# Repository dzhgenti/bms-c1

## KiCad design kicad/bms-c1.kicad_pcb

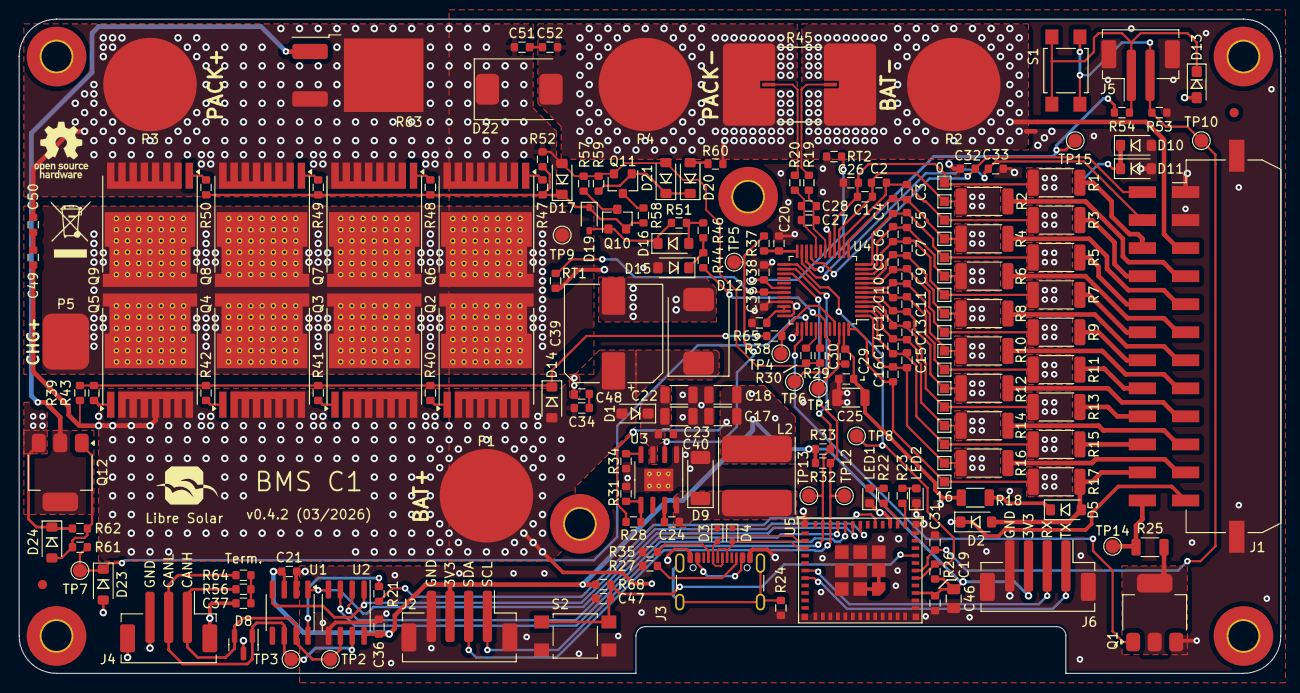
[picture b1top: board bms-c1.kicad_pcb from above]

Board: 4 copper layers, 135.0 x 70.0 mm, 209 parts (0 on the bottom side), 118 nets.

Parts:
C1, C2, C3, C4, C5, C6, C7, C8, C9, C10, C11, C12, C13, C14, C15, C16, C26: 220nF; C_0603_1608
C17, C18: 47µF; C_1206_3216
C19, C21, C24, C28, C31, C34, C36, C37, C40, C48, C49, C50, C51, C52: 100nF; C_0603_1608
C20: 2.2µF; C_0603_1608
C22, C23: 2.2µF; C_1206_3216
C25: 1µF; C_1206_3216
C27, C29, C32, C33, C35, C38: 100pF; C_0603_1608
C30, C47: 1µF; C_0603_1608
C39: 47uF; CP_Elec_10x10
C46: 10µF; C_0805_2012
D1, D13: PMEG10010ELRX; D_SOD-123F
D2, D5, D10, D15, D16, D20: BAT46W; D_SOD-123
D3, D4: ESD5B5.0ST1G; D_SOD-523
D8: PESD2CANFD; SOT-23
D9: VSS8D3M10-M3/I; D_SOD-128
D11: 3.6V; D_SOD-123
D12: SMCJ70A; D_SMC
D14, D17, D21, D24: 16V; D_SOD-123
D19: 5.1V; D_SOD-323
D22: MURS360; D_SMC
D23: 75V; D_SOD-123
FID1, FID2: Fiducial; Fiducial_1mm_Mask2mm
H1, H2, H3, H4, H5, H6: MountingHole; MountingHole_3.2mm_M3_Pad_TopBottom
J1: MicroFit 2x12; Molex_Micro-Fit_3.0_43045-2410_2x12-1MP_P3.00mm_Horizontal
J2, J6: B4B-PH-SM4; JST_PH_B4B-PH-SM4-TB_1x04-1MP_P2.00mm_Vertical
J3: USB_C_Receptacle_USB2.0; USB_C_Receptacle_GCT_USB4105-xx-A_16P_TopMnt_Horizontal
J4: B3B-PH-SM4; JST_PH_B3B-PH-SM4-TB_1x03-1MP_P2.00mm_Vertical
J5: B2B-PH-SM4; JST_PH_B2B-PH-SM4-TB_1x02-1MP_P2.00mm_Vertical
L2: 22µH; Bourns_SRN8040TA
LED1: LED red; LED_0603_1608Metric
LED2: LED green; LED_0603_1608Metric
LOGO1: OPEN_HARDWARE; OSHW-Logo_5.7x6mm_SilkScreen
LOGO2: LIBRE_SOLAR; LIBRESOLAR_LOGO
NT1: NetTie; NetTie-2_SMD_Pad0.5mm
P1, P2, P3, P4: CONN_01X01; Wuerth_PowerOne_SMD_LF990005
P5: CONN_01X01; SolderWirePad_1x01_SMD_5x10mm
Q1: DMN10H220LE; SOT-223
Q2, Q3, Q4, Q5, Q6, Q7, Q8, Q9: IPT012N08N5; Infineon_PG-HSOF-8-1_ThermalVias
Q10: BSS84; SOT-23
Q11: BSS123N; SOT-23
Q12: ZXMP10A17GTA; SOT-223-3_TabPin2
R1, R2, R3, R4, R5, R6, R7, R8, R9, R10, R11, R12, R13, R14, R15, R16, R17: 20; R_2010_5025
R18: 100; R_1206_3216
R19, R20, R38, R44: 100; R_0603_1608
R21, R37: 0R; R_0603_1608
R22, R23, R46: 1k; R_0603_1608
R24, R26, R62: 1M; R_0603_1608
R25: 10; R_1206_3216
R27, R35, R53, R54: 5.1k; R_0603_1608
R28, R65: 82k; R_0603_1608
R29, R30, R60, R68: 10k; R_0603_1608
R31: 35.7k; R_0603_1608
R32, R33: 2.2k; R_0603_1608
R34: 52.3k; R_0603_1608
R39, R52, R59: 10M; R_0603_1608
R40, R41, R42, R43, R47, R48, R49, R50, R57: 47; R_0603_1608
R45: 300µ; R_Shunt_5931_Kelvin
R51, R61: 68k; R_0603_1608
R56, R64: 62R; R_0603_1608
R58: 470; R_0603_1608
R63: 40; Bourns_PWR163
RT1, RT2: 10k; R_0603_1608
S1, S2: SW_PUSH; SW_SPST_TL3305A
TP1, TP2, TP3, TP4, TP5, TP6, TP7, TP8, TP9, TP10, TP12, TP13, TP14, TP15: TestPoint; TestPoint_Pad_D1.5mm
TP16, TP17, TP18, TP19, TP20, TP21, TP22, TP23, TP24, TP25, TP26, TP27, TP28, TP29, TP30, TP31, TP32: TestPoint; TestPoint_Pad_1.0x1.0mm
U1: SN65HVD230; SOIC-8_3.9x4.9mm_P1.27mm
U2: SN65HVD75; SOIC-8_3.9x4.9mm_P1.27mm
U3: LMR38010; SOIC-8-1EP_3.9x4.9mm_P1.27mm_EP2.4x3.1mm_ThermalVias
U4: BQ76952; TQFP-48_7x7mm_P0.5mm
U5: ESP32-C3-MINI-1

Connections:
+3V3: C17.1, C18.1, C19.1, C21.1, C36.1, C46.1, D13.2 (A), J2.3, J6.3, L2.2, R26.2, R28.1, R32.2, R33.2, R68.2, U1.3 (VCC), U2.8 (VCC), U5.3 (3V3)
/BAT+: C34.1, C39.1, C49.1, D1.2 (A), D2.1 (K), D12.1 (K), D14.2 (A), J1.12, P1.1, Q2.2 (S), Q3.2 (S), Q4.2 (S), Q5.2 (S), R39.2
/BAT-: C39.2, C48.2, D12.2 (A), J1.3, NT1.1, P2.1, R45.1
/BQ76952/ALERT: R26.1, TP8.1, U4.25 (ALERT), U5.5 (GPIO2/ADC1_CH2)
/BQ76952/BAT: C25.1, C29.1, C30.2, R18.1, U4.47 (BAT)
/BQ76952/BTN_HIGH: D13.1 (K), J5.1, R54.1, S1.2
/BQ76952/CHG: R38.1, TP4.1, U4.45 (CHG)
/BQ76952/CP1: C30.1, TP1.1, U4.46 (CP1)
/BQ76952/DSG: R44.1, TP6.1, U4.43 (DSG)
/BQ76952/LD: R30.1, U4.41 (LD)
/BQ76952/PACK: R29.1, U4.42 (PACK)
/BQ76952/PDSG: D23.1 (K), R61.1, TP7.1, U4.39 (PDSG)
/BQ76952/SHUNT_N: R20.1, R45.3
/BQ76952/SHUNT_P: R19.1, R45.2
/BQ76952/SRN: C27.2, C28.2, R20.2, U4.20 (SRN)
/BQ76952/SRP: C27.1, C28.1, R19.2, U4.18 (SRP)
/BQ76952/TEMP_SHUNT: C38.1, RT2.2, U4.30 (DFETOFF)
/BQ76952/VC0: C1.2, C26.1, D10.1 (K), D11.1 (K), R1.2, TP16.1, U4.16 (VC0)
/BQ76952/VC1: C1.1, C2.2, R2.2, TP17.1, U4.15 (VC1)
/BQ76952/VC2: C2.1, C3.2, R3.2, TP18.1, U4.14 (VC2)
/BQ76952/VC3: C3.1, C4.2, R4.2, TP19.1, U4.13 (VC3)
/BQ76952/VC4: C4.1, C5.2, R5.2, TP20.1, U4.12 (VC4)
/BQ76952/VC5: C5.1, C6.2, R6.2, TP21.1, U4.11 (VC5)
/BQ76952/VC6: C6.1, C7.2, R7.2, TP22.1, U4.10 (VC6)
/BQ76952/VC7: C7.1, C8.2, R8.2, TP23.1, U4.9 (VC7)
/BQ76952/VC8: C8.1, C9.2, R9.2, TP24.1, U4.8 (VC8)
/BQ76952/VC9: C9.1, C10.2, R10.2, TP25.1, U4.7 (VC9)
/BQ76952/VC10: C10.1, C11.2, R11.2, TP26.1, U4.6 (VC10)
/BQ76952/VC11: C11.1, C12.2, R12.2, TP27.1, U4.5 (VC11)
/BQ76952/VC12: C12.1, C13.2, R13.2, TP28.1, U4.4 (VC12)
/BQ76952/VC13: C13.1, C14.2, R14.2, TP29.1, U4.3 (VC13)
/BQ76952/VC14: C14.1, C15.2, R15.2, TP30.1, U4.2 (VC14)
/BQ76952/VC15: C15.1, C16.2, R16.2, TP31.1, U4.1 (VC15)
/BQ76952/VC16: C16.1, R17.2, TP32.1, U4.48 (VC16)
/BQ76952/WAKE: R54.2, TP15.1, U4.22 (TS2)
/BTN_LOW: C31.2, J5.2, R53.2, S1.1, TP10.1, U5.6 (GPIO3/ADC1_CH3)
/C1+: J1.4, R2.1
/C1-: J1.15, R1.1
/C2+: J1.16, R3.1
/C3+: J1.5, R4.1
/C4+: J1.17, R5.1
/C5+: J1.6, R6.1
/C6+: J1.18, R7.1
/C7+: J1.7, R8.1
/C8+: J1.19, R9.1
/C9+: J1.8, R10.1
/C10+: J1.20, R11.1
/C11+: J1.9, R12.1
/C12+: J1.21, R13.1
/C13+: J1.10, R14.1
/C14+: J1.22, R15.1
/C15+: J1.11, R16.1
/C16+: D2.2 (A), D5.2 (A), J1.23, R17.1
/CAN_H: D8.2 (K), J4.1, R56.1, TP2.1, U1.7 (CANH), U2.6 (A)
/CAN_L: D8.1 (K), J4.2, R64.2, TP3.1, U1.6 (CANL), U2.7 (B)
/CHG+: D24.1 (K), P5.1, Q2.3 (D), Q3.3 (D), Q4.3 (D), Q5.3 (D), Q6.3 (D), Q7.3 (D), Q8.3 (D), Q9.3 (D), Q12.3 (S), R62.1, TP9.1
/ESP32-C3 MCU/CAN_RX: U1.4 (R), U2.1 (R), U5.18 (GPIO4/ADC1_CH4)
/ESP32-C3 MCU/CAN_STB: R21.2, U5.16 (GPIO10)
/ESP32-C3 MCU/CAN_TX: U1.1 (D), U2.4 (D), U5.19 (GPIO5/ADC2_CH0)
/ESP32-C3 MCU/NRST: C47.1, R68.1, S2.2, U5.8 (EN/CHIP_PU)
/ESP32-C3 MCU/RS485_DE: U2.3 (DE), U5.20 (GPIO6)
/ESP32-C3 MCU/RS485_~RE: U2.2 (~RE), U5.21 (GPIO7)
/ESP32-C3 MCU/USB_D+: D4.2 (A2), J3.A6 (D+), J3.B6 (D+), U5.27 (GPIO19/USB_D+)
/ESP32-C3 MCU/USB_D-: D3.2 (A2), J3.A7 (D-), J3.B7 (D-), U5.26 (GPIO18/USB_D-)
/FUSE: J1.24, R25.2, TP14.1
/I2C_SCL: J2.1, R33.1, TP13.1, U4.26 (SCL), U5.23 (GPIO9)
/I2C_SDA: J2.2, R32.1, TP12.1, U4.27 (SDA), U5.22 (GPIO8)
/LED_GREEN: R23.2, U5.12 (GPIO0/ADC1_CH0/XTAL_32K_P)
/LED_RED: R22.2, U5.13 (GPIO1/ADC1_CH1/XTAL_32K_N)
/PACK+: C50.2, C51.1, D17.2 (A), D21.2 (A), D22.1 (K), P3.1, Q6.2 (S), Q7.2 (S), Q8.2 (S), Q9.2 (S), Q11.2 (S), R29.2, R30.2, R52.2, R57.1, R59.2, R63.2, R63.3
/PACK-: C52.2, D22.2 (A), P4.1, R45.4, R60.1
/Power Part/CHG_G: D14.1 (K), R38.2, R39.1, R40.1, R41.1, R42.1, R43.1
/Power Part/DSG_G: D17.1 (K), D19.1 (K), Q10.2 (S), R47.2, R48.2, R49.2, R50.2, R52.1, R58.1
/Power Supply/EN: R37.1, TP5.1, U3.2 (EN)
/Power Supply/FB: R28.2, R31.1, U3.5 (FB)
/Power Supply/SW: C24.2, D9.1 (K), L2.1, U3.8 (SW)
/Power Supply/VIN: C22.1, C23.1, C40.1, D1.1 (K), U3.3 (VIN)
/REG18: C20.1, R37.2, U4.24 (REG18)
/TEMP1: C32.1, J1.13, U4.21 (TS1)
/TEMP2: C33.1, J1.14, U4.23 (TS3)
/TEMP_FETS: C35.1, RT1.2, U4.31 (DCHG)
/UART_RX: J6.2, U5.30 (GPIO20/U0RXD)
/UART_TX: J6.1, U5.31 (GPIO21/U0TXD)
GND: C17.2, C18.2, C19.2, C20.2, C21.2, C22.2, C23.2, C25.2, C26.2, C29.2, C31.1, C32.2, C33.2, C35.2, C36.2, C37.2, C38.2, C40.2, C46.2, C47.2, D3.1 (A1), D4.1 (A1), D8.3 (A), D9.2 (A), D10.2 (A), D11.2 (A), D15.2 (A), D23.2 (A), J1.1, J1.2, J1.MP (MountPin), J2.4, J2.MP (MountPin), J3.A1 (GND), J3.A12 (GND), J3.B1 (GND), J3.B12 (GND), J4.3, J4.MP (MountPin), J5.MP (MountPin), J6.4, J6.MP (MountPin), LED1.1 (K), LED2.1 (K), NT1.2, Q1.3 (S), R24.1, R27.1, R31.2, R34.2, R35.1, R53.1, R65.2, RT1.1, RT2.1, S2.1, U1.2 (GND), U2.5 (GND), U3.1 (GND), U3.9 (PADGND), U4.17 (VSS), U4.33 (RST_SHUT), U4.36 (REGIN), U4.37 (BREG), U5.1 (GND), U5.2 (GND), U5.11 (GND), U5.14 (GND), U5.36 (GND)
unnamed: C34.2, C48.1
unnamed: C37.1, R56.2, R64.1
unnamed: C49.2, C50.1
unnamed: C51.2, C52.1
unnamed: D5.1 (K), R18.2
unnamed: D15.1 (K), R44.2, R46.1
unnamed: D16.2 (A), R46.2, R51.1
unnamed: D16.1 (K), D19.2 (A), Q10.1 (G), R51.2
unnamed: D20.2 (A), R60.2
unnamed: D20.1 (K), D21.1 (K), Q11.1 (G), R59.1
unnamed: D24.2 (A), Q12.1 (G), R61.2, R62.2
unnamed: J3.A5 (CC1), R35.2
unnamed: J3.B5 (CC2), R27.2
unnamed: J3.S1 (SHIELD), R24.2
unnamed: J3.A4 (VBUS), J3.A9 (VBUS), J3.B4 (VBUS), J3.B9 (VBUS)
unnamed: LED1.2 (A), R22.1
unnamed: LED2.2 (A), R23.1
unnamed: Q1.2 (D), Q1.4 (D), R25.1
unnamed: Q1.1 (G), U4.38 (FUSE)
unnamed: Q2.1 (G), R40.2
unnamed: Q3.1 (G), R41.2
unnamed: Q4.1 (G), R42.2
unnamed: Q5.1 (G), R43.2
unnamed: Q6.1 (G), R47.1
unnamed: Q7.1 (G), R48.1
unnamed: Q8.1 (G), R49.1
unnamed: Q9.1 (G), R50.1
unnamed: Q10.3 (D), R57.2
unnamed: Q11.3 (D), R58.2
unnamed: Q12.2 (D), R63.1
unnamed: R21.1, U1.8 (Rs)
unnamed: C24.1, U3.7 (BOOT)
unnamed: R34.1, U3.4 (RT/SYNC)
unnamed: R65.1, U4.34 (REG2), U4.35 (REG1)

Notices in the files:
kicad/bms-c1.kicad_pcb:
License: CERN-OHL-W
